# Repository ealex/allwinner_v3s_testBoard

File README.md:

# allwinner_v3s_testBoard
Test project based on the Allwinner V3S SOC

The project will contain a basic board with power supplies and ethernet.
Most of the digital IO is exposed on the board edge as 2.54mm headers
SD0 interface is used for boot.

The "buildroot" folder contais all the required files and instructions to build a bare system.

Please keep in mind that the board is build around my requirements.

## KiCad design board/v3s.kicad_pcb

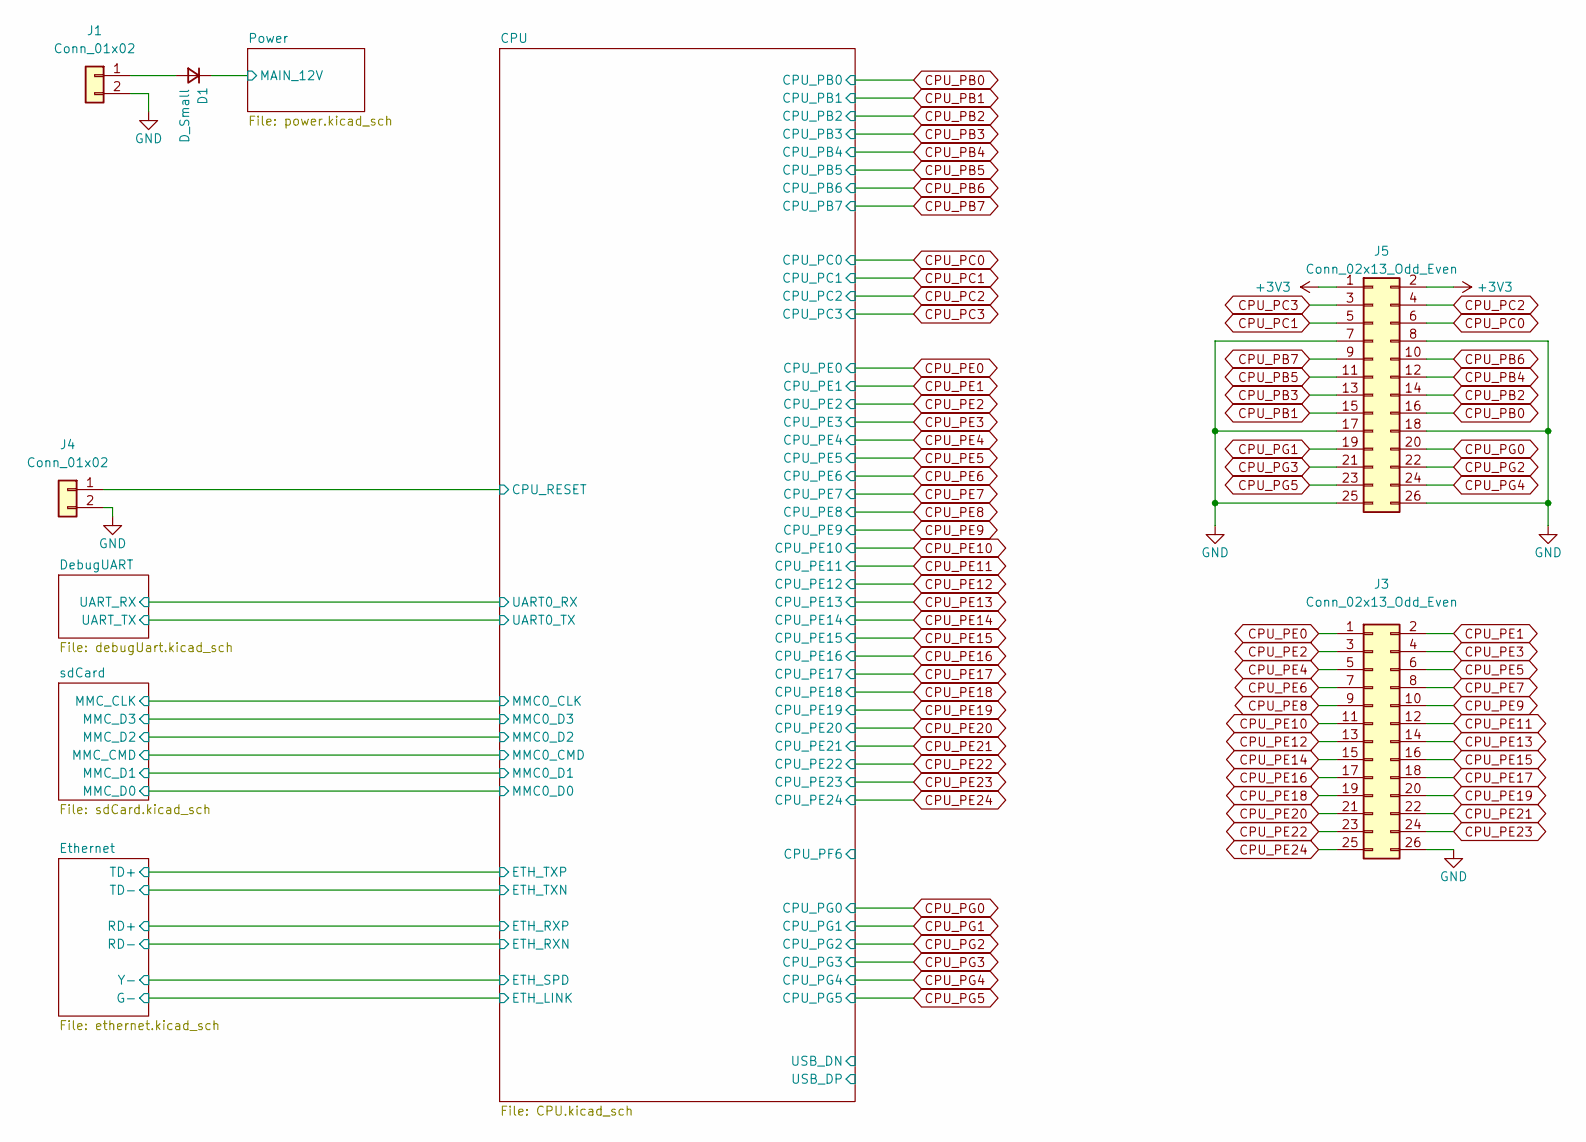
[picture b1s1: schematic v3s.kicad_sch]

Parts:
D1: D_Small; D_SMA
J1: Conn_01x02; JST_PH_B2B-PH-K_1x02_P2.00mm_Vertical
J3, J5: Conn_02x13_Odd_Even; PinHeader_2x13_P2.54mm_Vertical
J4: Conn_01x02; PinHeader_1x02_P2.54mm_Vertical

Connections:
+3V3: J5.1, J5.2; also elsewhere on the board
+12V: D1.1 (K); also elsewhere on the board
/CPU/CPU_RESET: J4.1; also elsewhere on the board
CPU_PB0: J5.16; also elsewhere on the board
CPU_PB1: J5.15; also elsewhere on the board
CPU_PB2: J5.14; also elsewhere on the board
CPU_PB3: J5.13; also elsewhere on the board
CPU_PB4: J5.12; also elsewhere on the board
CPU_PB5: J5.11; also elsewhere on the board
CPU_PB6: J5.10; also elsewhere on the board
CPU_PB7: J5.9; also elsewhere on the board
CPU_PC0: J5.6; also elsewhere on the board
CPU_PC1: J5.5; also elsewhere on the board
CPU_PC2: J5.4; also elsewhere on the board
CPU_PC3: J5.3; also elsewhere on the board
CPU_PE0: J3.1; also elsewhere on the board
CPU_PE1: J3.2; also elsewhere on the board
CPU_PE2: J3.3; also elsewhere on the board
CPU_PE3: J3.4; also elsewhere on the board
CPU_PE4: J3.5; also elsewhere on the board
CPU_PE5: J3.6; also elsewhere on the board
CPU_PE6: J3.7; also elsewhere on the board
CPU_PE7: J3.8; also elsewhere on the board
CPU_PE8: J3.9; also elsewhere on the board
CPU_PE9: J3.10; also elsewhere on the board
CPU_PE10: J3.11; also elsewhere on the board
CPU_PE11: J3.12; also elsewhere on the board
CPU_PE12: J3.13; also elsewhere on the board
CPU_PE13: J3.14; also elsewhere on the board
CPU_PE14: J3.15; also elsewhere on the board
CPU_PE15: J3.16; also elsewhere on the board
CPU_PE16: J3.17; also elsewhere on the board
CPU_PE17: J3.18; also elsewhere on the board
CPU_PE18: J3.19; also elsewhere on the board
CPU_PE19: J3.20; also elsewhere on the board
CPU_PE20: J3.21; also elsewhere on the board
CPU_PE21: J3.22; also elsewhere on the board
CPU_PE22: J3.23; also elsewhere on the board
CPU_PE23: J3.24; also elsewhere on the board
CPU_PE24: J3.25; also elsewhere on the board
CPU_PG0: J5.20; also elsewhere on the board
CPU_PG1: J5.19; also elsewhere on the board
CPU_PG2: J5.22; also elsewhere on the board
CPU_PG3: J5.21; also elsewhere on the board
CPU_PG4: J5.24; also elsewhere on the board
CPU_PG5: J5.23; also elsewhere on the board
GND: J1.2, J3.26, J4.2, J5.7, J5.8, J5.17, J5.18, J5.25, J5.26; also elsewhere on the board
unnamed: D1.2 (A), J1.1

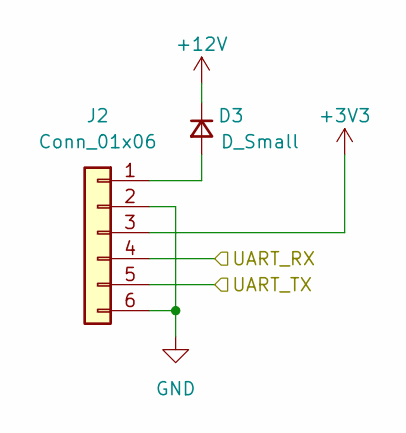
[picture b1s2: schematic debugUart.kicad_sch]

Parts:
D3: D_Small; D_SMA
J2: Conn_01x06; JST_PH_B6B-PH-K_1x06_P2.00mm_Vertical

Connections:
+3V3: J2.3; also elsewhere on the board
+12V: D3.1 (K); also elsewhere on the board
/CPU/UART0_RX: J2.4; also elsewhere on the board
/CPU/UART0_TX: J2.5; also elsewhere on the board
GND: J2.2, J2.6; also elsewhere on the board
unnamed: D3.2 (A), J2.1

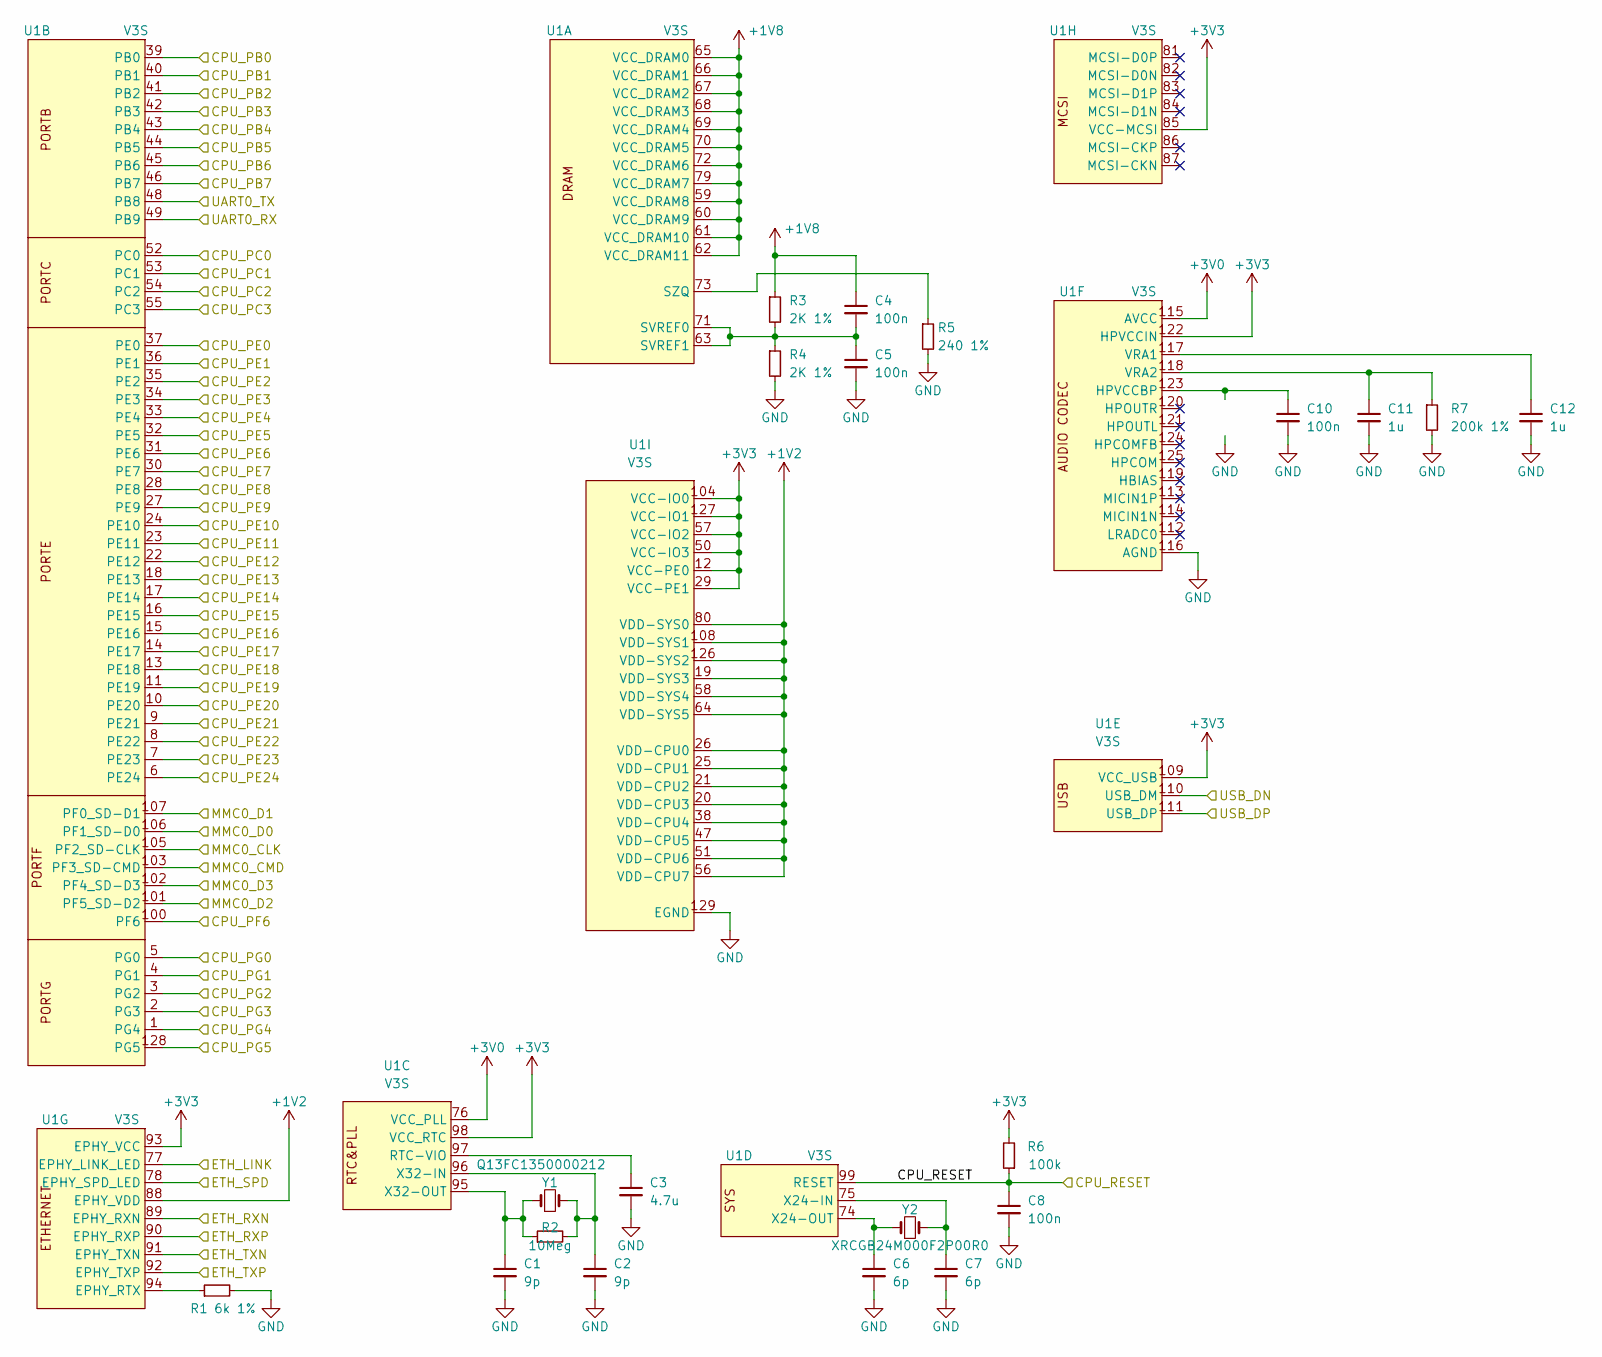
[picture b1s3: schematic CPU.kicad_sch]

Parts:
C1, C2: 9p; C_0603_1608Metric
C3: 4.7u; C_0603_1608Metric
C4, C5, C8, C10: 100n; C_0603_1608Metric
C6, C7: 6p; C_0603_1608Metric
C11, C12: 1u; C_0603_1608Metric
R1: 6k 1%; R_0603_1608Metric
R2: 10Meg; R_0603_1608Metric
R3, R4: 2K 1%; R_0603_1608Metric
R5: 240 1%; R_0603_1608Metric
R6: 100k; R_0603_1608Metric
R7: 200k 1%; R_0603_1608Metric
U1: V3S; LQFP-128_14x14mm_P0.4mm_EP8x8mm
Y1: Q13FC1350000212; Crystal_SMD_3215-2Pin_3.2x1.5mm
Y2: XRCGB24M000F2P00R0

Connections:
+1V2: U1.19 (VDD-SYS3), U1.20 (VDD-CPU3), U1.21 (VDD-CPU2), U1.25 (VDD-CPU1), U1.26 (VDD-CPU0), U1.38 (VDD-CPU4), U1.47 (VDD-CPU5), U1.51 (VDD-CPU6), U1.56 (VDD-CPU7), U1.58 (VDD-SYS4), U1.64 (VDD-SYS5), U1.80 (VDD-SYS0), U1.88 (EPHY_VDD), U1.108 (VDD-SYS1), U1.126 (VDD-SYS2); also elsewhere on the board
+1V8: C4.1, R3.1, U1.59 (VCC_DRAM8), U1.60 (VCC_DRAM9), U1.61 (VCC_DRAM10), U1.62 (VCC_DRAM11), U1.65 (VCC_DRAM0), U1.66 (VCC_DRAM1), U1.67 (VCC_DRAM2), U1.68 (VCC_DRAM3), U1.69 (VCC_DRAM4), U1.70 (VCC_DRAM5), U1.72 (VCC_DRAM6), U1.79 (VCC_DRAM7); also elsewhere on the board
+3V0: U1.76 (VCC_PLL), U1.115 (AVCC); also elsewhere on the board
+3V3: R6.2, U1.12 (VCC-PE0), U1.29 (VCC-PE1), U1.50 (VCC-IO3), U1.57 (VCC-IO2), U1.85 (VCC-MCSI), U1.93 (EPHY_VCC), U1.98 (VCC_RTC), U1.104 (VCC-IO0), U1.109 (VCC_USB), U1.122 (HPVCCIN), U1.127 (VCC-IO1); also elsewhere on the board
/CPU/CPU_PF6: U1.100 (PF6)
/CPU/CPU_RESET: C8.1, R6.1, U1.99 (RESET); also elsewhere on the board
/CPU/ETH_LINK: U1.77 (EPHY_LINK_LED); also elsewhere on the board
/CPU/ETH_RXN: U1.89 (EPHY_RXN); also elsewhere on the board
/CPU/ETH_RXP: U1.90 (EPHY_RXP); also elsewhere on the board
/CPU/ETH_SPD: U1.78 (EPHY_SPD_LED); also elsewhere on the board
/CPU/ETH_TXN: U1.91 (EPHY_TXN); also elsewhere on the board
/CPU/ETH_TXP: U1.92 (EPHY_TXP); also elsewhere on the board
/CPU/MMC0_CLK: U1.105 (PF2_SD-CLK); also elsewhere on the board
/CPU/MMC0_CMD: U1.103 (PF3_SD-CMD); also elsewhere on the board
/CPU/MMC0_D0: U1.106 (PF1_SD-D0); also elsewhere on the board
/CPU/MMC0_D1: U1.107 (PF0_SD-D1); also elsewhere on the board
/CPU/MMC0_D2: U1.101 (PF5_SD-D2); also elsewhere on the board
/CPU/MMC0_D3: U1.102 (PF4_SD-D3); also elsewhere on the board
/CPU/UART0_RX: U1.49 (PB9); also elsewhere on the board
/CPU/UART0_TX: U1.48 (PB8); also elsewhere on the board
/CPU/USB_DN: U1.110 (USB_DM)
/CPU/USB_DP: U1.111 (USB_DP)
CPU_PB0: U1.39 (PB0); also elsewhere on the board
CPU_PB1: U1.40 (PB1); also elsewhere on the board
CPU_PB2: U1.41 (PB2); also elsewhere on the board
CPU_PB3: U1.42 (PB3); also elsewhere on the board
CPU_PB4: U1.43 (PB4); also elsewhere on the board
CPU_PB5: U1.44 (PB5); also elsewhere on the board
CPU_PB6: U1.45 (PB6); also elsewhere on the board
CPU_PB7: U1.46 (PB7); also elsewhere on the board
CPU_PC0: U1.52 (PC0); also elsewhere on the board
CPU_PC1: U1.53 (PC1); also elsewhere on the board
CPU_PC2: U1.54 (PC2); also elsewhere on the board
CPU_PC3: U1.55 (PC3); also elsewhere on the board
CPU_PE0: U1.37 (PE0); also elsewhere on the board
CPU_PE1: U1.36 (PE1); also elsewhere on the board
CPU_PE2: U1.35 (PE2); also elsewhere on the board
CPU_PE3: U1.34 (PE3); also elsewhere on the board
CPU_PE4: U1.33 (PE4); also elsewhere on the board
CPU_PE5: U1.32 (PE5); also elsewhere on the board
CPU_PE6: U1.31 (PE6); also elsewhere on the board
CPU_PE7: U1.30 (PE7); also elsewhere on the board
CPU_PE8: U1.28 (PE8); also elsewhere on the board
CPU_PE9: U1.27 (PE9); also elsewhere on the board
CPU_PE10: U1.24 (PE10); also elsewhere on the board
CPU_PE11: U1.23 (PE11); also elsewhere on the board
CPU_PE12: U1.22 (PE12); also elsewhere on the board
CPU_PE13: U1.18 (PE13); also elsewhere on the board
CPU_PE14: U1.17 (PE14); also elsewhere on the board
CPU_PE15: U1.16 (PE15); also elsewhere on the board
CPU_PE16: U1.15 (PE16); also elsewhere on the board
CPU_PE17: U1.14 (PE17); also elsewhere on the board
CPU_PE18: U1.13 (PE18); also elsewhere on the board
CPU_PE19: U1.11 (PE19); also elsewhere on the board
CPU_PE20: U1.10 (PE20); also elsewhere on the board
CPU_PE21: U1.9 (PE21); also elsewhere on the board
CPU_PE22: U1.8 (PE22); also elsewhere on the board
CPU_PE23: U1.7 (PE23); also elsewhere on the board
CPU_PE24: U1.6 (PE24); also elsewhere on the board
CPU_PG0: U1.5 (PG0); also elsewhere on the board
CPU_PG1: U1.4 (PG1); also elsewhere on the board
CPU_PG2: U1.3 (PG2); also elsewhere on the board
CPU_PG3: U1.2 (PG3); also elsewhere on the board
CPU_PG4: U1.1 (PG4); also elsewhere on the board
CPU_PG5: U1.128 (PG5); also elsewhere on the board
GND: C1.2, C2.2, C3.2, C5.2, C6.2, C7.2, C8.2, C10.2, C11.2, C12.2, R1.2, R4.2, R5.2, R7.2, U1.116 (AGND), U1.129 (EGND); also elsewhere on the board
unnamed: C1.1, R2.1, U1.95 (X32-OUT), Y1.1
unnamed: C2.1, R2.2, U1.96 (X32-IN), Y1.2
unnamed: C3.1, U1.97 (RTC-VIO)
unnamed: C4.2, C5.1, R3.2, R4.1, U1.63 (SVREF1), U1.71 (SVREF0)
unnamed: C6.1, U1.74 (X24-OUT), Y2.1
unnamed: C7.1, U1.75 (X24-IN), Y2.2
unnamed: C10.1, U1.123 (HPVCCBP)
unnamed: C11.1, R7.1, U1.118 (VRA2)
unnamed: C12.1, U1.117 (VRA1)
unnamed: R1.1, U1.94 (EPHY_RTX)
unnamed: R5.1, U1.73 (SZQ)

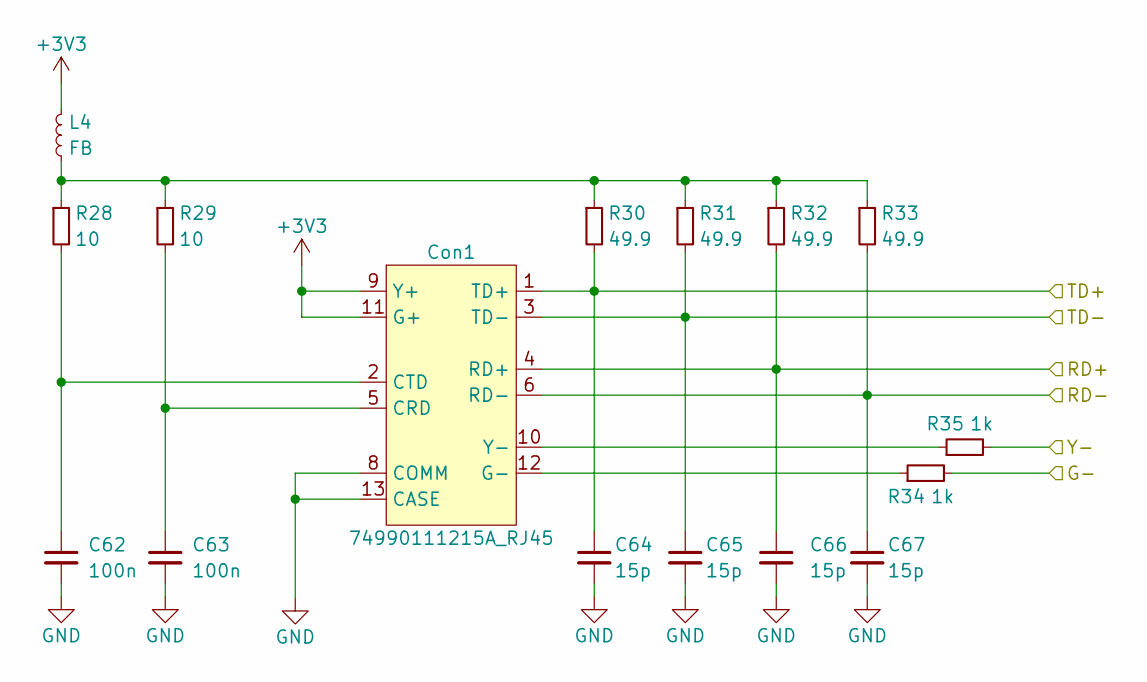
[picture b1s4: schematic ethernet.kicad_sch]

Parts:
C62, C63: 100n; C_0603_1608Metric
C64, C65, C66, C67: 15p; C_0603_1608Metric
Con1: 74990111215A_RJ45
L4: FB; R_0805_2012Metric
R28, R29: 10; R_0603_1608Metric
R30, R31, R32, R33: 49.9; R_0603_1608Metric
R34, R35: 1k; R_0603_1608Metric

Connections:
+3V3: Con1.9 (Y+), Con1.11 (G+), L4.2; also elsewhere on the board
/CPU/ETH_LINK: R34.2; also elsewhere on the board
/CPU/ETH_RXN: C67.1, Con1.6 (RD-), R33.2; also elsewhere on the board
/CPU/ETH_RXP: C66.1, Con1.4 (RD+), R32.2; also elsewhere on the board
/CPU/ETH_SPD: R35.2; also elsewhere on the board
/CPU/ETH_TXN: C65.1, Con1.3 (TD-), R31.2; also elsewhere on the board
/CPU/ETH_TXP: C64.1, Con1.1 (TD+), R30.2; also elsewhere on the board
GND: C62.2, C63.2, C64.2, C65.2, C66.2, C67.2, Con1.8 (COMM), Con1.13 (CASE); also elsewhere on the board
unnamed: C62.1, Con1.2 (CTD), R28.2
unnamed: C63.1, Con1.5 (CRD), R29.2
unnamed: Con1.10 (Y-), R35.1
unnamed: Con1.12 (G-), R34.1
unnamed: L4.1, R28.1, R29.1, R30.1, R31.1, R32.1, R33.1

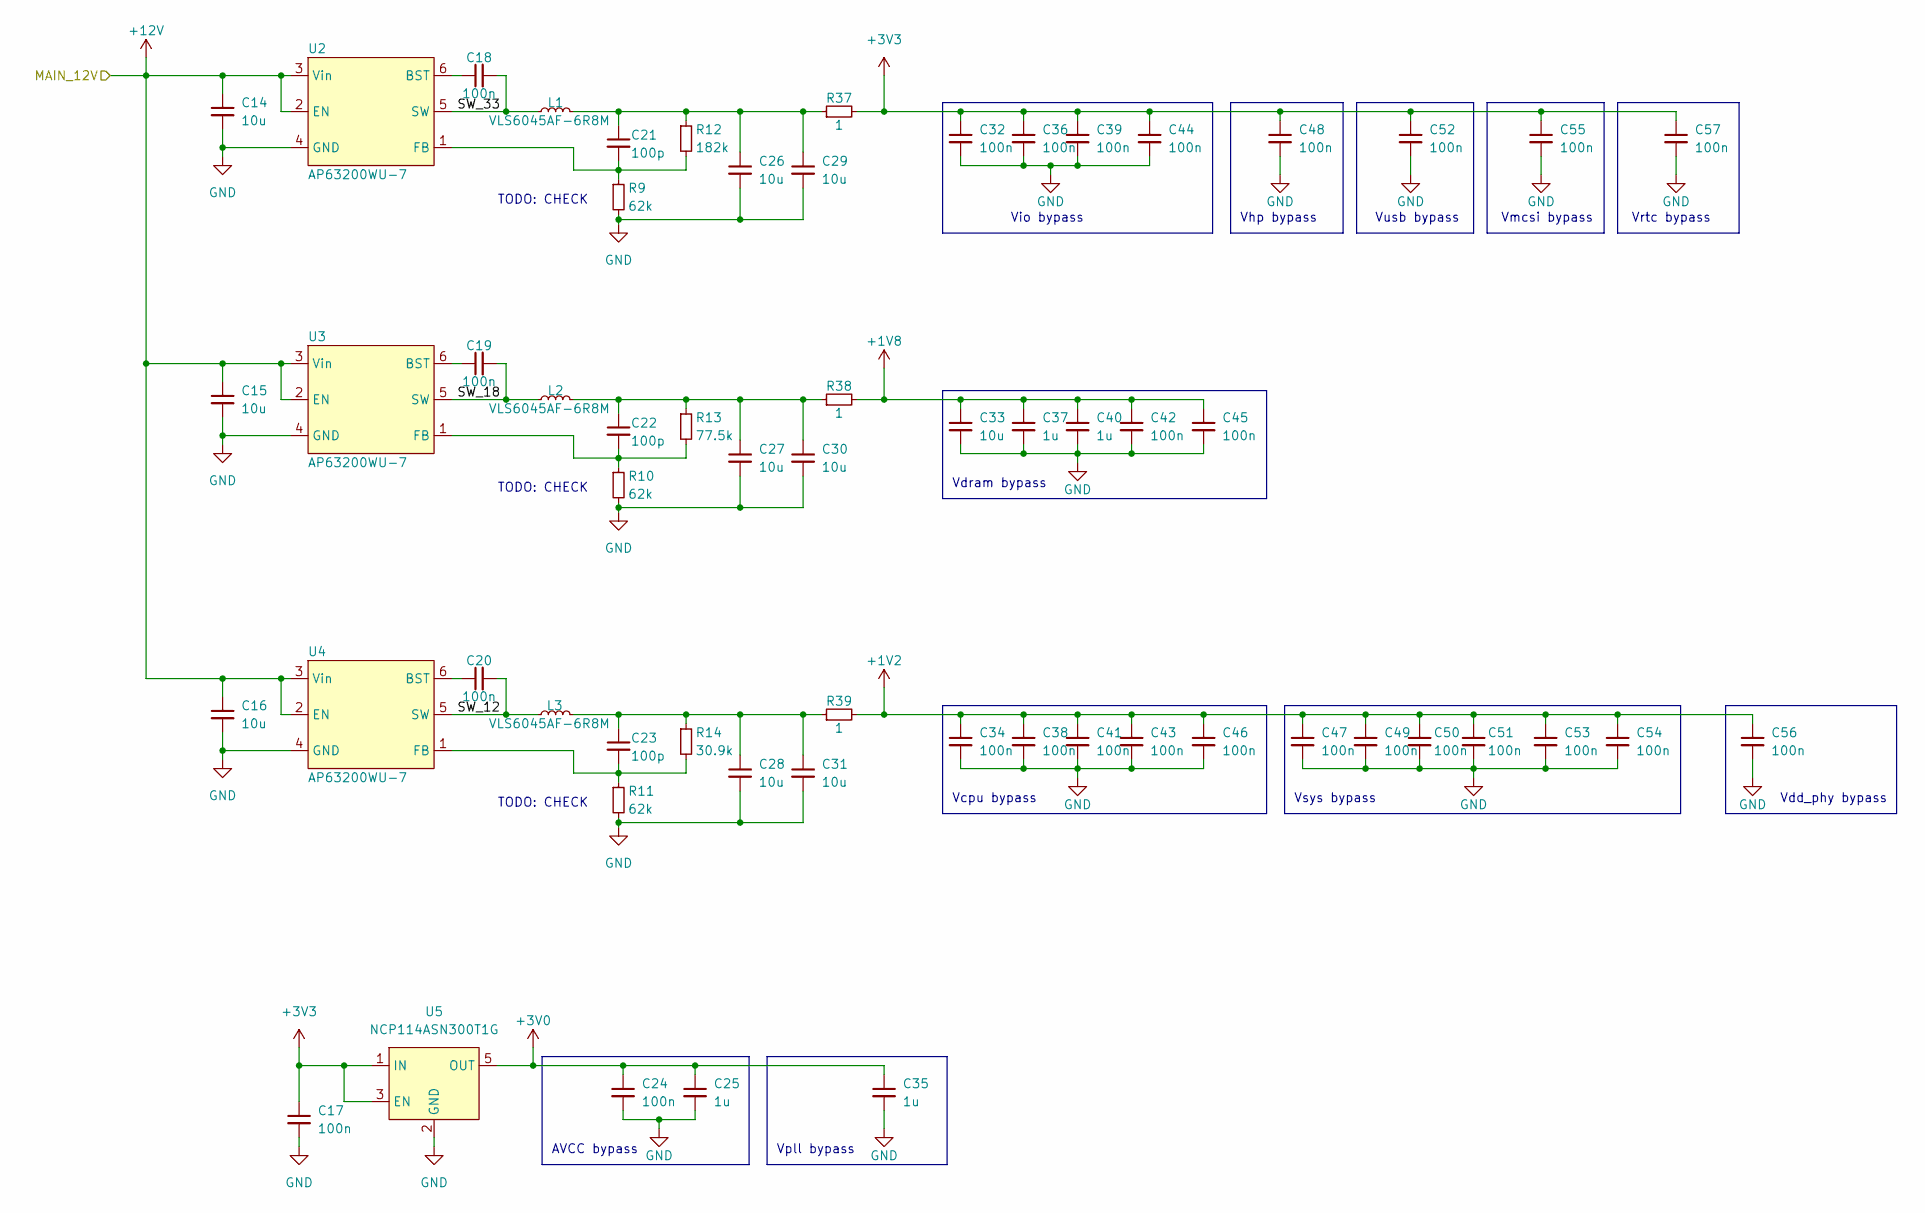
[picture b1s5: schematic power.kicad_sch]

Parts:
C14, C15, C16, C26, C27, C28, C29, C30, C31, C33: 10u; C_0603_1608Metric
C17, C18, C19, C20, C24, C32, C34, C36, C38, C39, C41, C42, C43, C44, C45, C46, C47, C48, C49, C50, C51, C52, C53, C54, C55, C56, C57: 100n; C_0603_1608Metric
C21, C22, C23: 100p; C_0603_1608Metric
C25, C35, C37, C40: 1u; C_0603_1608Metric
L1, L2, L3: VLS6045AF-6R8M; NRS6045T6R8
R9, R10, R11: 62k; R_0603_1608Metric
R12: 182k; R_0603_1608Metric
R13: 77.5k; R_0603_1608Metric
R14: 30.9k; R_0603_1608Metric
R37, R38, R39: 1; R_1206_3216Metric
U2, U3, U4: AP63200WU-7; TSOT26
U5: NCP114ASN300T1G; SOT-23-5

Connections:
+1V2: C34.1, C38.1, C41.1, C43.1, C46.1, C47.1, C49.1, C50.1, C51.1, C53.1, C54.1, C56.1, R39.2; also elsewhere on the board
+1V8: C33.1, C37.1, C40.1, C42.1, C45.1, R38.2; also elsewhere on the board
+3V0: C24.1, C25.1, C35.1, U5.5 (OUT); also elsewhere on the board
+3V3: C17.1, C32.1, C36.1, C39.1, C44.1, C48.1, C52.1, C55.1, C57.1, R37.2, U5.1 (IN), U5.3 (EN); also elsewhere on the board
+12V: C14.1, C15.1, C16.1, U2.2 (EN), U2.3 (Vin), U3.2 (EN), U3.3 (Vin), U4.2 (EN), U4.3 (Vin); also elsewhere on the board
/Power/SW_12: C20.2, L3.1, U4.5 (SW)
/Power/SW_18: C19.2, L2.1, U3.5 (SW)
/Power/SW_33: C18.2, L1.1, U2.5 (SW)
GND: C14.2, C15.2, C16.2, C17.2, C24.2, C25.2, C26.2, C27.2, C28.2, C29.2, C30.2, C31.2, C32.2, C33.2, C34.2, C35.2, C36.2, C37.2, C38.2, C39.2, C40.2, C41.2, C42.2, C43.2, C44.2, C45.2, C46.2, C47.2, C48.2, C49.2, C50.2, C51.2, C52.2, C53.2, C54.2, C55.2, C56.2, C57.2, R9.2, R10.2, R11.2, U2.4 (GND), U3.4 (GND), U4.4 (GND), U5.2 (GND); also elsewhere on the board
unnamed: C18.1, U2.6 (BST)
unnamed: C19.1, U3.6 (BST)
unnamed: C20.1, U4.6 (BST)
unnamed: C21.1, C26.1, C29.1, L1.2, R12.1, R37.1
unnamed: C21.2, R9.1, R12.2, U2.1 (FB)
unnamed: C22.1, C27.1, C30.1, L2.2, R13.1, R38.1
unnamed: C22.2, R10.1, R13.2, U3.1 (FB)
unnamed: C23.1, C28.1, C31.1, L3.2, R14.1, R39.1
unnamed: C23.2, R11.1, R14.2, U4.1 (FB)

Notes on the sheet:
Vpll bypass
TODO: CHECK
Vmcsi bypass
Vdd_phy bypass
Vhp bypass
Vrtc bypass
Vdram bypass
AVCC bypass
Vsys bypass
Vio bypass
Vcpu bypass
Vusb bypass

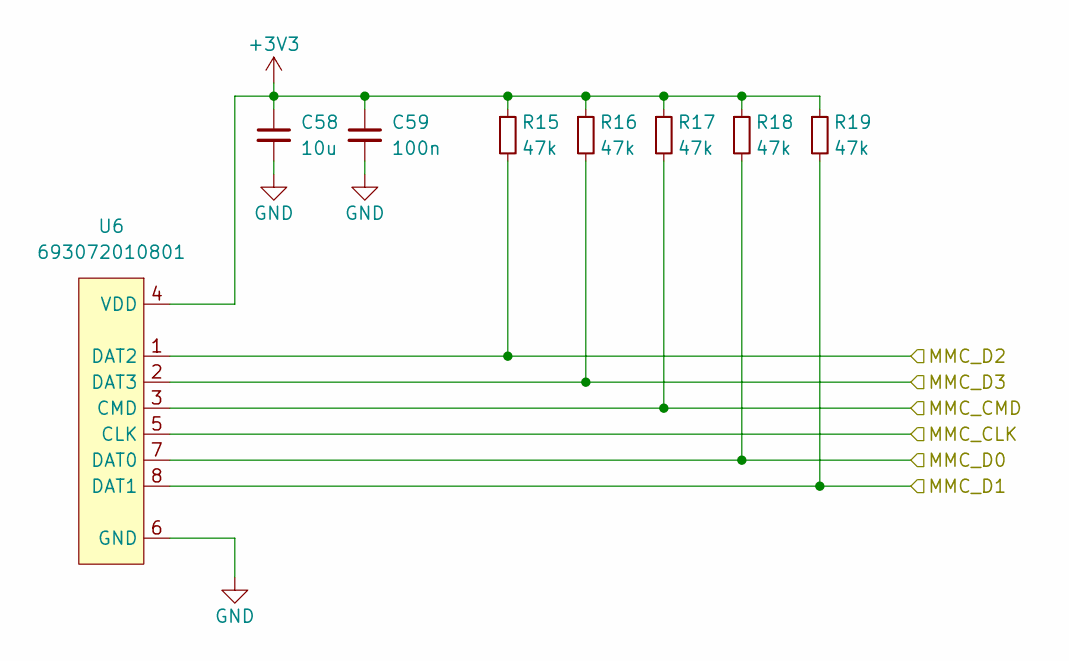
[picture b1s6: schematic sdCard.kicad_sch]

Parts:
C58: 10u; C_0603_1608Metric
C59: 100n; C_0603_1608Metric
R15, R16, R17, R18, R19: 47k; R_0603_1608Metric
U6: 693072010801

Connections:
+3V3: C58.1, C59.1, R15.1, R16.1, R17.1, R18.1, R19.1, U6.4 (VDD); also elsewhere on the board
/CPU/MMC0_CLK: U6.5 (CLK); also elsewhere on the board
/CPU/MMC0_CMD: R17.2, U6.3 (CMD); also elsewhere on the board
/CPU/MMC0_D0: R18.2, U6.7 (DAT0); also elsewhere on the board
/CPU/MMC0_D1: R19.2, U6.8 (DAT1); also elsewhere on the board
/CPU/MMC0_D2: R15.2, U6.1 (DAT2); also elsewhere on the board
/CPU/MMC0_D3: R16.2, U6.2 (DAT3); also elsewhere on the board
GND: C58.2, C59.2, U6.6 (GND); also elsewhere on the board

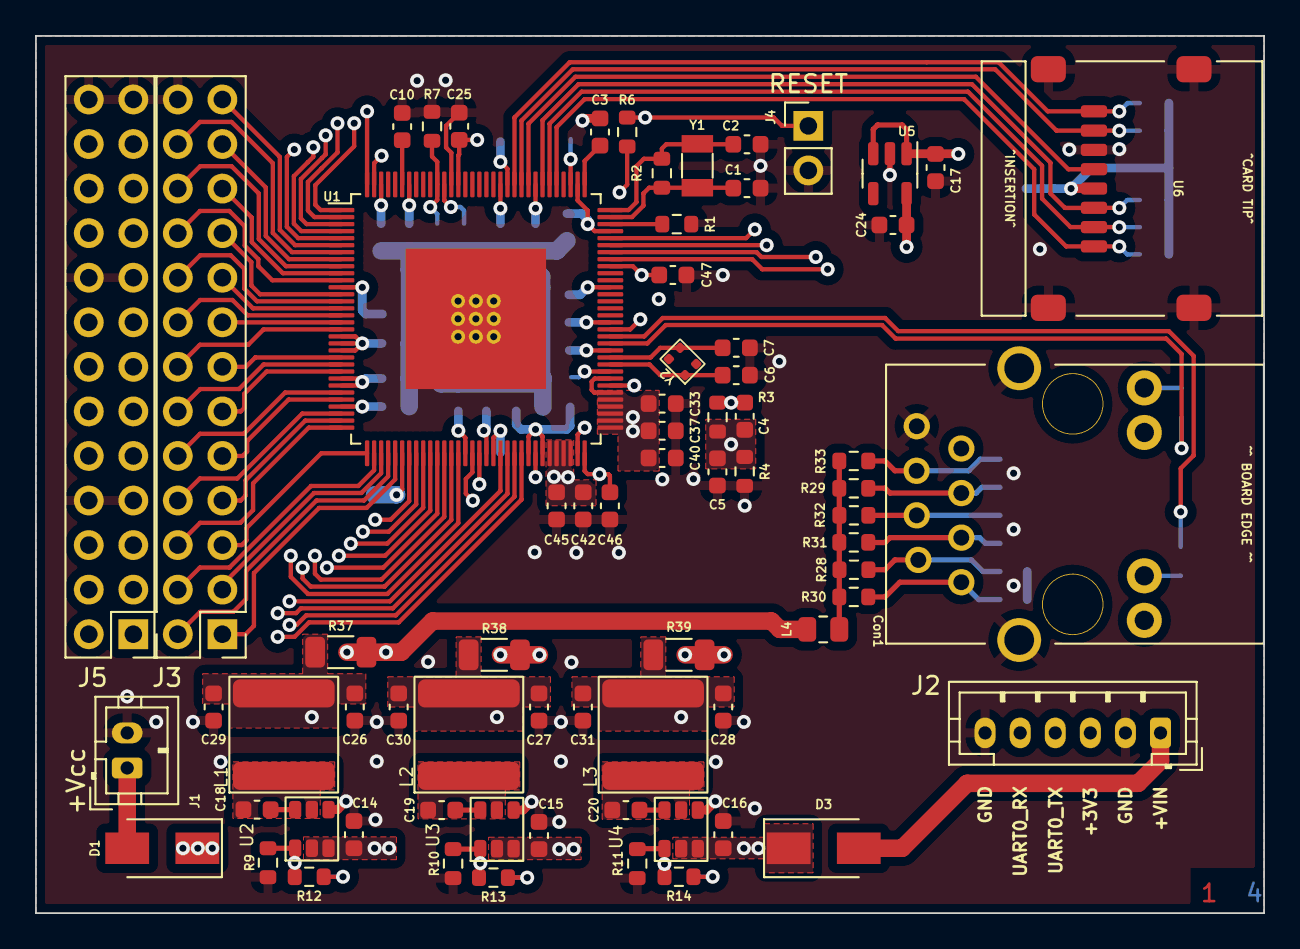
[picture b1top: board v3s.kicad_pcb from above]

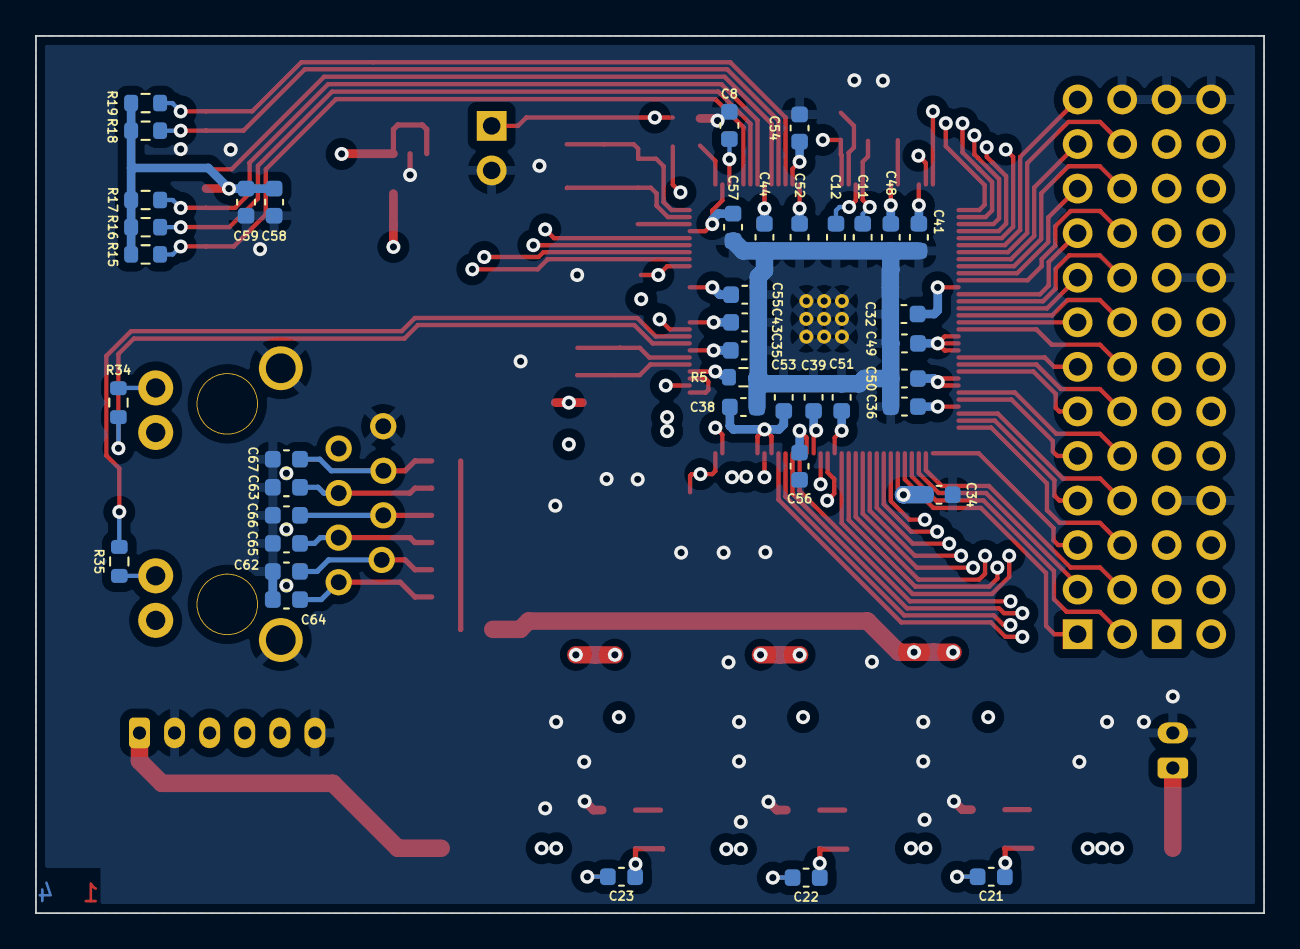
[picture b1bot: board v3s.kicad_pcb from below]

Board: 4 copper layers, 70.0 x 50.0 mm, 112 parts (41 on the bottom side), 94 nets.

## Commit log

2022-08-26 add v3s documentation and sample project
2022-08-26 add current schematic
2022-10-03 add kicad gitignore
2022-10-03 schematic update, choose components, creeate footprints
2022-10-03 export schematic as pdf
2022-10-07 pcb layout
2022-11-05 update layout
2023-01-14 updates, finish layout, remove usb-uart
2023-01-14 Test
2023-01-14 test2
2023-01-14 test3
